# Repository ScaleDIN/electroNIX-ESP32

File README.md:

# electroNIX → ESP32 rewiring guide

**Use `BOARD_ELECTRONIX_4` for any 4-tube build and `BOARD_ELECTRONIX_4_6T`
for any 6-tube build.** These two board definitions cover every supported
TESTA-QUADRA PCB. The Nick2 IN-12 is a completely different design and is
documented separately below.

If you are retrofitting an older board that uses an **IRF840** boost MOSFET
(electroNIX 2 PCB, fourTINY) rather than the logic-level **IRLR3110Z** of the
electroNIX 4, you need a gate driver — see the *IRF840 boards* section under
electroNIX 4+S.

> ## ⚠️ 170 V is present on every board
> The boost output and all the driver stages carry ~170 VDC. The output
> capacitors hold charge after power-off. Unplug, wait, and verify with a
> meter before touching anything. Never rewire with power applied.

## Strategy: leave the ATmega in place, hold it in reset

You don't have to desolder the TQFP-44 on any of these boards. Grounding its
**RESET (pin 4)** puts every AVR pin into high-impedance, freeing all the
driver nets. One short wire from the RESET pad (or the ISP header JP1) to GND
and the chip is out of the picture.

Pick up the signals at the **resistors** they feed — larger pads, no
fine-pitch soldering. Every driver on every board is an active-high NPN base
behind a series resistor, so 3.3 V logic drives them directly with no level
shifters needed on any output.

---

# electroNIX 4 — recommended 4-tube target

`#define BOARD BOARD_ELECTRONIX_4`

Logic-level **IRLR3110Z** boost switch — drives directly from 3.3 V, no gate
driver needed.

## Signal map

| Net | Tap point | ESP32 GPIO | Notes |
|---|---|---|---|
| `C_0`…`C_9` cathodes | **R22–R31** (33 k) | 13, 14, 21, 22, 23, 25, 26, 27, 32, 33 | Designators are not in net order — see below. |
| `W_1`…`W_4` anodes | **R15, R14, R17, R16** (33 k) | 16, 17, 18, 19 | |
| `SEC_0`, `SEC_1` colons | **R18, R19** (430 k) | 4, 5 | See *Colon wiring* in the 4+S section. |
| `PWM` boost gate | **R59** (10 Ω at Q50) | 2 | IRLR3110Z, logic-level, drive directly. |
| `KOMP_170V` | **R60 / R61** junction | 35 (input) | |
| `JASNOSC` | **R63 / D1** junction | 34 (input) | R63 pulls up to **+5V_BUF** — lift its supply end and rewire to ESP32 **3V3** before connecting GPIO34. |
| `MEL` buzzer | **R62** (2 k) | **0** | GPIO0 is a strapping pin. Fit ≥10 kΩ pull-up to 3V3. `cfg.buzzerEn` defaults false. GPIO12 is free. |
| IR receiver (IR1) | IR1 pad | 39 (input, reserved) | Power IR1 from 3V3, not +5V_BUF. Not decoded yet. |
| DS3231 SDA (optional) | I2C bus | 1 | 4.7 kΩ pull-up to 3V3. |
| DS3231 SCL (optional) | I2C bus | 3 | 4.7 kΩ pull-up to 3V3. |
| Buttons S1–S3 | switch leg | 36 (optional) | External 10 k to 3V3 required — GPIO36 has no internal pull-up. |

GPIO1, GPIO3, and GPIO12 are all free when no DS3231 is fitted.

## Cathode designators are not in net order

This trips people up on every TESTA board: resistor numbers do not run in the
same order as `C_0`…`C_9`. Wire them in any convenient order, then fix any
scrambling in software using **Pin check** — you never have to resolder.

**Maintenance → Pin check → digits**: hold `0`, note what digit the tubes
actually show, repeat for `1`–`9`. Type the ten observations into the *Digits
shown for 0–9* field and save. The display is then correct. Re-open the page
and the field reads `0,1,2,…,9` — that's the confirmation.

**Tube positions** work the same way via *Pin check → tubes*: click each
position button, note which tube lights, record the physical order in *Tube
positions*. Digits and tube positions can be fixed independently and in either
order.

---

# electroNIX 4+S — recommended 6-tube target

`#define BOARD BOARD_ELECTRONIX_4_6T`

The electroNIX 4 expanded to six tubes with a seconds pair. Every cathode,
both colon outputs, the HV PWM pin, and all sensors stay on exactly the same
GPIOs as the 4-tube board. This definition also covers **fresh ESP32 retrofits
of the electroNIX 2 PCB** — use it in place of the obsolete
`BOARD_ELECTRONIX_2`.

## GPIO changes from the electroNIX 4

The electroNIX 4 uses all comfortable output GPIOs. The two extra anode
outputs and the optional LED backlight come from reassigning the buzzer and
reclaiming the two strapping pins:

| GPIO | Role on electroNIX 4 | Role on electroNIX 4+S |
|---|---|---|
| **0** | Unused | `MEL` buzzer (strapping pin — 10 kΩ pull-up to 3V3 required) |
| **12** | `MEL` buzzer | `W_5` anode — seconds tens tube (no pull-up needed) |
| **15** | Unused | `W_6` anode *or* LED backlight — see below (strapping pin — 10 kΩ pull-up to 3V3 required) |
| **1** | Free | DS3231 SDA — *or* `W_6` anode when LED backlight fitted |
| **3** | Free | DS3231 SCL |

## Pull-ups on GPIO0 and GPIO15

Both are strapping pins. GPIO0 drives the buzzer (normally LOW); GPIO15 drives
the W_6 anode or LED backlight BJT base through a 33 kΩ series resistor. Both
conditions pull those pins below the 2.31 V HIGH threshold at reset, which can
cause spurious download-mode entry.

**Fit 10 kΩ from GPIO0 to 3V3 and 10 kΩ from GPIO15 to 3V3.** GPIO12 (W_5)
is not a strapping pin and needs no pull-up.

## Colon wiring — SEC_0 and SEC_1

`SEC_0` (GPIO4) and `SEC_1` (GPIO5) are two independent drive outputs. The
firmware controls them with whatever colon mode is configured (STEADY, BLINK,
BREATHE, ALTERNATE, etc.) — what you connect to them is entirely up to you.
Common arrangements:

- **Single neon per colon position**: wire one neon to `SEC_0`, leave `SEC_1`
  unconnected. Set `BOARD_DUAL_NEON 0` in `board.h`.
- **Top and bottom dots, both positions**: wire all top neons in parallel to
  `SEC_0` and all bottom neons in parallel to `SEC_1`. ALTERNATE then steps
  top on → bottom on across all positions simultaneously.
- **Independent per-position control**: wire all HH:MM neons to `SEC_0` and
  all MM:SS neons to `SEC_1`.

Any arrangement works — the firmware fires GPIO4 and GPIO5 on every tick
regardless of what's physically connected. Set `BOARD_DUAL_NEON 1` whenever
two outputs are wired; set `BOARD_DUP_COLON 1` only if the web UI preview
should mirror the HH:MM colon state onto MM:SS (no firmware effect otherwise).

## Optional LED backlight (electroNIX 2 PCB only)

The electroNIX 2 PCB has an under-tube LED backlight chain (R17 → Q3). To
enable it:

1. **Wire R17 to GPIO15.** GPIO15 becomes `PIN_LEDBL`, PWM'd at 1 kHz. The
   10 kΩ pull-up already fitted on GPIO15 is sufficient.
2. **Wire W_6 (R42) to GPIO1.** GPIO1 was the original LED drive pin before
   the DS3231 retrofit; it reverts to active use here. The bootloader drives
   it briefly at reset — through a 33 kΩ base resistor with no HV on the
   rail, the tube cannot strike.
3. **Set `BOARD_HAS_LED_BL 1`** in the profile in `board.h`. The firmware
   remaps `ANODE_PINS[5]` to GPIO1 and sets `PIN_LEDBL = 15` automatically.
4. **Leave `BOARD_HAS_RTC 0`.** GPIO1 cannot be both W_6 and DS3231 SDA. The
   firmware issues a compile-time error if both flags are set.

## Signal map

| Net | Tap point | ESP32 GPIO | Notes |
|---|---|---|---|
| `C_0`…`C_9` cathodes | **R22–R31** (33 k) | 13, 14, 21, 22, 23, 25, 26, 27, 32, 33 | **Identical to the electroNIX 4.** |
| `W_1`…`W_4` anodes | **R15, R14, R17, R16** (33 k) | 16, 17, 18, 19 | **Identical.** |
| `W_5` anode (seconds tens) | 33 k base resistor | **12** | GPIO12, former buzzer. No pull-up needed. |
| `W_6` anode (seconds units) | 33 k base resistor | **15** *(no LED)* or **1** *(LED)* | See LED backlight section above. |
| `LED` backlight | **R17** (33 k, base of Q3) — electroNIX 2 PCB only | **15** *(when fitted)* | Mutually exclusive with DS3231 RTC. |
| `SEC_0`, `SEC_1` colons | 430 k base resistors | 4, 5 | **Identical to the electroNIX 4.** See *Colon wiring* above. |
| `PWM` boost gate | **R59** (10 Ω at Q50) | 2 | IRLR3110Z, logic-level. Identical. |
| `KOMP_170V` | **R60 / R61** junction | 35 (input) | Identical. |
| `JASNOSC` | **R63 / D1** junction | 34 (input) | Lift R63's +5V_BUF end to 3V3. Identical. |
| `MEL` buzzer | **R62** (2 k) | **0** | Strapping pin. 10 kΩ pull-up to 3V3. `cfg.buzzerEn` defaults false. |
| DS3231 SDA (optional) | I2C bus | **1** *(no LED)* | Unavailable when LED backlight fitted. 4.7 kΩ pull-up to 3V3. |
| DS3231 SCL (optional) | I2C bus | 3 | 4.7 kΩ pull-up to 3V3. |
| Buttons S1–S3 | switch leg | 36 (optional) | External 10 k to 3V3. |

## Matching the seconds tubes

Seconds tubes often sit behind different emitter resistors and look dimmer at
equal duty. Use the **per-tube trim** row in the web UI — six percentages — to
even them out without touching the hardware.

## IRF840 boards — gate driver required

The electroNIX 2 PCB and fourTINY use an **IRF840** boost MOSFET. This is a
standard-level part specified at Vgs = 10 V; at 3.3 V it will either not turn
on at all or turn on partially and overheat. **Fit a gate driver before
connecting the PWM wire.** Options:

1. **Gate driver (recommended):** TC4420, MCP1407, or UCC27517 from the
   board's +12 V rail. ESP32 GPIO2 → driver input, driver output → gate
   resistor → Q5 gate. Non-inverting — leave `HV_PWM_INVERT 0`.
2. **Discrete level shifter:** a 2N7002 with a pull-up to +12 V. This
   **inverts** — set `HV_PWM_INVERT 1`. Check Q5 doesn't run hot; the 2N7002
   is slower than a real driver.
3. **Swap the FET:** replace with a logic-level 500 V part. Uncommon;
   options 1 and 2 are usually easier.

The sketch refuses to build for an IRF840 board until `HV_GATE_FITTED 1` is
set in `board.h` — this is deliberate.

Also check the gate resistor on the fourTINY: **R50** is shown as 10 k on
that schematic, which may be a pull-down rather than a series resistor — 10 k
in series with the gate at 32 kHz is far too slow. Confirm with a meter before
powering up.

---

# Nick2 IN-12 — different architecture

`#define BOARD BOARD_NICK2`

The Nick2 is not a TESTA-QUADRA board. Where TESTA drives cathodes directly
from individual GPIOs, Nick2 uses a **74141 BCD decoder** — four GPIO bits
select which of the ten cathodes conducts, so a single chip replaces ten
transistors. The colon is a column of **five WS2812B addressable LEDs** rather
than neon lamps.

## Signal map (schematic rev 2.0, 2021-03-09)

| Net | ESP32 GPIO | Notes |
|---|---|---|
| 74141 input A (LSB) | 4 | BCD digit select — shared across all tubes. |
| 74141 input B | 17 | |
| 74141 input C | 5 | |
| 74141 input D (MSB) | 16 | |
| Anode 1 | 32 | One GPIO per tube — multiplexed by the ISR. |
| Anode 2 | 33 | |
| Anode 3 | 25 | |
| Anode 4 | 26 | |
| WS2812B chain | 3 (UART RX) | 5 LEDs per column: 1 decorative top, 2 colon dots, 1 colon dot, 1 decorative / warning bottom. |
| `JASNOSC` (optional) | 34 (input) | If a light sensor is fitted. |
| DS3231 SDA (optional) | 21 | Standard ESP32 I2C pins — no strapping-pin concerns. |
| DS3231 SCL (optional) | 22 | |

If your board revision uses different GPIOs, the runtime endpoint
`POST /api/action?do=setpin&kind=an&idx=0&gpio=32` writes to NVS and
reboots. `kind=an` for anode 0–3, `kind=bcd` for 74141 inputs A–D (0–3).
Alternatively define `PIN_BCD_A` etc. in `board.h` before including it.

## Colon LEDs

The five WS2812B LEDs are addressed 0–4 top to bottom. LEDs 1 and 3 (the two
colon dots) are driven by the colon mode; LEDs 0, 2, and 4 are decorative and
configurable separately. LED 4 (bottom) doubles as the *time not trusted*
warning — it blinks regardless of colon mode until a trusted time source
(NTP, RTC, or browser sync) is established.

If your column is physically upside-down, tick **colonReversed** in the web
UI to flip the mapping without rewiring.

---

# Deprecated board targets

The following board definitions remain in the firmware but are no longer
the recommended retrofit target. Use `BOARD_ELECTRONIX_4` or
`BOARD_ELECTRONIX_4_6T` for new builds.

## electroNIX 3 (`BOARD_ELECTRONIX_3`)

4-tube, logic-level IRLR3110ZPBF boost switch, **USB power only** (no 12 V
rail — a boost + diode-capacitor multiplier ladder runs directly from 5 V).
The GPIO map is identical to the electroNIX 4 except the light sensor pull-up
resistor is 1 M (R44) to +5V rather than +5V_BUF — lift it to 3V3 the same
way.

Only one colon neon is fitted from the factory (`SEC_0` only); a second can
be added as a bodge to the ATmega's PB1 pad and wired to GPIO5. Tick **Second
colon neon fitted** in the web UI once done.

Power: feed the ESP32's **5V/VIN** from `+5V_BUF` (D19 + bulk caps). Do not
feed a GPIO from the USB rail. The boost duty ceiling (`HV_DUTY_MAX` in
`display_testa.cpp`) may need raising on this board — watch `duty` and `hv`
in the status bar on first power-up.

## electroNIX 2 (`BOARD_ELECTRONIX_2` — obsolete)

PCB-030/031, 6-tube, **IRF840** boost switch. Use `BOARD_ELECTRONIX_4_6T`
for fresh retrofits of this PCB. A gate driver is required — see the *IRF840
boards* section above. Set `BOARD_HAS_LED_BL 1` if the under-tube LED
backlight chain (R17/Q3) is fitted. The cathode resistors are numbered R56–R65
in a scrambled order; use **Pin check** to sort them out in software rather
than reordering the wires.

## fourTINY (`BOARD_FOURTINY`)

4-tube (LC-516), **IRF840** boost switch — gate driver required. GPIO map is
identical to the electroNIX 4; use `BOARD_ELECTRONIX_4` for new builds unless
you have a specific reason to keep `BOARD_FOURTINY`. Confirm R50 is a
pull-down (not a series gate resistor) before powering up.

---

# Shared notes

## Power

**Do not power the ESP32 from the 78M05.** WiFi current peaks (300–500 mA)
dissipate ~3 W in a linear regulator fed from 12 V. Either:

1. Replace U1 with a pin-compatible switcher (OKI-78SR-5/1.5-W36-C, Traco
   TSR 1-2450) and feed the ESP32's **5V/VIN** from the board's 5 V rail, or
2. Add a small buck module (MP1584 / "mini-360" set to 5 V) from the 12 V
   input directly to the ESP32's **5V/VIN**, leaving the 78M05 to serve the
   original 5 V loads.

Never feed `+5V_BUF` into an ESP32 GPIO. The 3V3 pin powers only the
`JASNOSC` pull-up and any button pull-ups.

## Drive strength

At 3.3 V through 33 k base resistors the MPSA42 switches get ~80 µA of base
drive — enough for typical cathode current, but with less margin than at 5 V.
If a digit looks dim or ghosting appears, parallel the relevant 33 k with
another 33 k (or drop to 10 k). Most builds don't need this.

## Bring-up procedure

1. Set `BOARD` in the sketch. Wire everything **except** the `PWM` line.
   Ground the ATmega's RESET.
2. Power up. The ESP32 starts an access point **ElectroNIX-Setup** (password
   `nixie1234`). Connect, open `http://192.168.4.1`, enter WiFi and timezone,
   save — it reboots and joins your network as `http://electronix.local`.
3. Check the status bar: **HV** should read ≈0 V and duty should climb, then
   report *FAULT* after about a second — that's the sense-fault protection
   confirming the feedback wire on GPIO35 is being read. Power-cycle to clear.
4. Power off, discharge, connect the `PWM` wire (through the gate driver on
   IRF840 boards). Power on: HV should ramp to 170 V within a second and the
   tubes light. Measure the real voltage and set *HV sense trim* so the
   reported value matches.
5. Fix any digit or tube-order scrambling with **Pin check** as described in
   the electroNIX 4 section above.

## Settings and firmware updates

From **2.13.0** settings survive firmware updates — each setting lives under
its own NVS key, so a new version that adds a setting finds that key missing
and uses its default; everything else is read back untouched.

Use **Back up settings** and **Restore** before flashing anything
experimental or when setting up a second clock. The wiring order and per-tube
trims come along with it; the WiFi password is deliberately excluded.

## Running without NTP

Three fallbacks in order of accuracy:

1. **NTP** — shown as `time  NTP · 3m ago` in the status bar. Default poll
   interval 60 minutes, adjustable from 5 minutes to a day; *correct smoothly*
   slews rather than steps, so corrections never make seconds tubes skip.
2. **Browser sync** — opening the web page silently takes the time from your
   device if no network time is available. Works over the clock's own AP with
   no internet at all.
3. **Restored estimate** — written to flash hourly, shown as *estimated* in
   amber until a real sync arrives.

For a permanently offline clock, add a DS3231 — see below.

## Cleaning cycles

Nixie cathodes that rarely light can develop a haze; running them clears it.
Under *Maintenance*, set **Cleaning cycle** (how often, in minutes; 0 to
disable), **Cycle length** (1–60 seconds), and **Cycle style**:

- *Slot machine* — all tubes spin, then settle one at a time from the left.
- *Every digit in turn* — steps through 0–9 in equal slices, offset per tube.
  This one actually does the job: every cathode gets exactly the same
  conduction time.

## If the display flickers

**Check the status bar first.** The second line shows **core 0 / core 1**
load, **mux** (multiplex interrupt rate as a percentage of expected 40 kHz),
and **hv cuts**.

- **mux dips below 100%** — an interrupt stalled. From 2.15.0 the time
  snapshot is written to RTC memory (free, survives resets) and flash only
  every six hours, and that write waits for tubes-dark moments. If mux still
  dips, check that *Core Debug Level* is set to **None** in the IDE.
- **hv cuts climbing** — the boost regulator backed off on a noisy ADC sample.
  Check the HV sense trim calibration and the smoothing capacitors at the boost
  output (C2–C5 on the v4 schematic).

OTA updates deliberately blank the display for the transfer duration and then
reboot — a clean blank rather than a flicker is intentional.

**Arduino IDE settings that matter:**
- CPU Frequency: **240 MHz**
- Core Debug Level: **None**
- Erase All Flash Before Sketch Upload: **Disabled** (unless you want to lose settings)

## If the light sensor isn't doing anything

The status bar shows the sensor live as `light  1840 mV · 42%`. Watch it
while you cover the phototransistor.

1. **Reading says "railed" and never moves** — the 5 V pull-up mod hasn't
   been done. Lift the supply end of R63 (v4) / R11 (v2) / R57 (fourTINY) /
   R44 (v3) and rewire to ESP32 **3V3**.
2. **Reading moves but the tubes don't** — auto brightness must be ticked on.
   Also check that *min* and *max* aren't set to the same value.
3. **Moves over a narrow band** — calibrate using *use current as dark* and
   *as bright* in the web UI. A wider calibration span reduces the effect of
   ADC noise.
4. **Noisy reading** — add **100 nF ceramic** from GPIO34 to GND. This alone
   usually fixes it; the high-impedance pull-up can't recharge the ADC's
   sampling capacitor fast enough without it. Also consider lowering the
   pull-up from 1 M to 100 k, keeping the sensor wire short, and routing it
   away from the boost inductor.

---

# DS3231 real-time clock (optional, all boards)

A battery-backed DS3231 module lets the clock wake at the correct time
immediately after a mains outage without waiting for NTP. The status panel
shows **RTC** in green rather than *estimated* in amber.

## Enable in firmware

In `board.h`, above the `#define BOARD` line:

```c
#define BOARD_HAS_RTC 1
```

To override the default SDA/SCL pins:

```c
#define BOARD_RTC_SDA  0
#define BOARD_RTC_SCL 15
#define BOARD_HAS_RTC  1
```

## Default I2C pins

| Board family | SDA | SCL |
|---|---|---|
| All TESTA boards (4, 4+S, 3) | GPIO1 | GPIO3 |
| Nick2 IN-12 | GPIO21 | GPIO22 |

**4.7 kΩ pull-ups** from SDA to 3V3 and SCL to 3V3 are required. Most DS3231
breakout modules include them — check for R2/R3 on the silkscreen.

The DS3231 I2C pins are not strapping pins on any board. The 10 kΩ pull-up
requirements in the 4+S section above are for GPIO0 (buzzer) and GPIO15
(anode / LED backlight) — not for the I2C lines.

## Fit the CR2032 before powering up

Without it the DS3231 loses its time the moment the clock is unplugged. The
cell lasts several years in standby. When exhausted the DS3231 resets to
2000-01-01; the firmware detects this (year < 2020) and falls back to the NVS
epoch rather than displaying the year 2000.

## How it integrates with NTP

- **At boot**: the DS3231 is read before WiFi starts — the correct time
  appears within milliseconds, and `timeTrusted` is set immediately.
- **At NTP sync**: the DS3231 is updated to the NTP-corrected time.
- **Browser sync**: the posted epoch is written to the DS3231 and persists
  across power cuts — useful when NTP is blocked on your network.
- **No WiFi**: the DS3231 keeps time at ±2 ppm (≈ ±0.2 s/day) on the
  backup cell.

---

## Firmware safety features

- Boost gate is off during boot and flashing (GPIO2 boot pull-down).
- Software regulation: absolute duty clamp (~41 %), soft-start ramp, hard
  over-voltage cut at target + 12 V, shutdown if the feedback divider reads
  open — the converter will not run open-loop.
- HV shuts down whenever the tubes are off (night mode at 0 %, web toggle).
- 25 µs inter-digit blanking prevents ghosting between tubes.

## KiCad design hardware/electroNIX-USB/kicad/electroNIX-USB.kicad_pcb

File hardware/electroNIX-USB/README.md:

# electroNIX-USB — USB-C powered ESP32 nixie clock (4 or 6 × Z573M)

A new KiCad design: an ESP32 version of the TESTA-QUADRA **electroNIXclock 3**
(PCB-036, 2013). That was the micro-USB powered board; its schematic is filed as
`original electronix clock/z573m/schema_204xZ573M.pdf`. The tube is the RFT Z573M.
A Z566M variant comes later.

**Status (work in progress):** schematics are done for 4 and 6 tubes. The
4-tube PCB (`kicad/electroNIX-USB.kicad_pcb`, 102 × 66 mm, the original
kit's size) and the 6-tube PCB (`kicad-6tube/`, 150 × 66 mm) are **placed
but not routed**. Route them in KiCad (Freerouting plugin, fanout off),
then add the GND pours on both layers.

| Path | Contents |
|---|---|
| `kicad/` | **4-tube** KiCad project (HH:MM): root sheet plus 4 sub-sheets, project symbol library (`electronix.kicad_sym`: Z573M, `+170V`) and footprint library (`electronix.pretty`: `Nixie_RFT_Z573M`) |
| `kicad-6tube/` | **6-tube** KiCad project (HH:MM:SS), same layout of sheets |
| `electroNIX-USB-{4,6}tube-schematic.pdf` | Plots of all 5 sheets |
| `electroNIX-USB-{4,6}tube-bom.csv` | BOMs grouped by value and footprint |
| `source/gen.py` | Generator: `python3 source/gen.py kicad` or `python3 source/gen.py kicad-6tube --tubes 6` |
| `source/pcb.py` | Board builder: places parts from the netlist, autoroutes with Freerouting, pours GND, runs DRC (`--place-only` stops after placement) |
| `source/fab.sh` | Gerbers, drill files and pick-and-place zip for a board |
| `source/footprint.py` | Writes the Z573M footprint: `python3 source/footprint.py kicad/electronix.pretty` |

The files are in KiCad 7 format, so KiCad 7, 8 and 9 all open them (8 and 9
upgrade on save). Once you start editing in KiCad, the KiCad files are the
source and the generator is only a record of the first pass. Don't re-run it
over hand edits.

## Sheets

1. **Power & USB:** USB-C receptacle wired as a 5 V sink (5k1 on CC1/CC2),
   polyfuse, SMBJ5.0CA TVS, 22 µF/35 V tantalum bulk, USBLC6-2SC6 on D+/D−, AMS1117-3.3, and CH340C
   for programming and serial log.
2. **ESP32:** ESP32-WROOM-32E, two-transistor DTR/RTS auto-reset, and the
   light sensor. **No switches:** the firmware is set up from its web UI
   and reads no button. The CH340C resets the chip and puts it into
   download mode, and unplugging USB is the reset. If auto-reset ever
   fails, short the IO0 pull-up to GND while plugging in. No buzzer and
   no RTC: time
   comes from NTP.
3. **HV supply:** the PCB-036 converter. IO2 drives an IRLR3110Z into a
   33 µH WE 7447715330 (22 µH on the 6-tube build). The switch node feeds a
   7-diode / 7-capacitor Cockcroft-Walton ladder (10MQ100N, 2.2 µF/100 V)
   that makes 170 V. Feedback is 430k/6k2, the same ratio as
   `HV_DIV_RATIO`.
4. **Display:** 4 or 6 × Z573M. Anodes are switched high-side (MMBTA42
   level shift into MMBTA92, 5k6 or 3k9 anode resistor). 10 shared MMBTA42
   cathode switches. The 1N4148 off-cathode clamp to a ~32 V bias is kept
   from PCB-036. Colon neons.

## Z573M (RFT data book p.101/103)

Source: [frank.pocnet.net/sheets/084/z/Z573M.pdf](https://frank.pocnet.net/sheets/084/z/Z573M.pdf).
Z5730M is the same tube without the contrast-filter coating.

- **Tube:** side-view, 13 mm digits, decimal point on the right. Bulb is
  Ø19 × 47.6 mm with 38 mm flying leads.
- **Pinout:** 1–3 = k1–k3, 4 = ic (internal, leave open), 5–9 = k4–k8,
  10 = dp, 11 = k9, 12 = k0, 13 = anode. This matches the symbol.
- **Lead layout:** 13 leads on a **Ø9.53 mm** circle in 14 equal
  positions (25.7°), with the gap opposite **wire 7, which faces the
  front**.
- **Electrical:** V_ign 150 V, V_maint 140 V, V_ext 120 V, minimum supply
  170 V. **Cathode current 1.5–2.5 mA continuous, 12 mA pulse maximum.**

### Footprint `electronix:Nixie_RFT_Z573M`

- **Geometry:** a top view with wire 7 toward +Y, so the board's front
  edge goes toward +Y. The data book draws the leads from below,
  numbered clockwise; on the footprint they run counter-clockwise. Pad 1
  is square.
- **Pads:** 0.8 mm drill, 1.35 mm pad, 2.12 mm centre spacing.
- **Silkscreen:** references are 0.8 mm. Each sits right beside its own
  part (within ~1 mm, and closer to its own part than to any other) or,
  where there's no room, inside the part between its pads (the ladder
  caps). Labels never overlap other labels, part outlines, pads or the
  board edge.
- **KBIAS network** (430k, 100k, 4 × 470 nF series string) sits in the
  free space under the colon, between the tube 2 and tube 3 anode
  clusters.
- **ESP32 footprint:** the stock footprint's 48 mm-wide keep-out and
  matching courtyard are replaced by a body-sized courtyard plus a board
  keep-out under the antenna. The module sits 0.3 mm inside the back edge.
  Minimum drill is 0.2 mm for the module's exposed-pad vias.
- **Known DRC item:** the USB-C footprint's locating pegs are 0.19 mm from
  its own pads (stock GCT USB4105 footprint). Exclude it in DRC.
- **Net classes:** HV (0.4 mm clearance) for +170 V, anodes, the ladder
  and the neon nets; Power (0.5 mm track) for GND/+5V/+3V3/VBUS.

## Open points (check before or during layout)

- **Neon footprints** are still unassigned. Pick the lamp (NE-2 or INS-1)
  with the layout.
- **WE 7447715330:** the KiCad footprint is WE-PD "Typ LS" (12 × 12 mm),
  which is the same series as the 7447715906 in its datasheet link.
  Confirm 33 µH and the saturation current (≥ 2.5 A) when ordering. For
  the 6-tube build's 22 µH, `7447715220` is inferred from the same part
  numbering: check that it exists and that I_sat ≥ 3 A.
- **ERC:** the KiCad 7 command line here has no ERC, so I checked
  connectivity on the exported netlist instead. No single-pin nets, every
  driver chain was traced, and the multiplier matches PCB-036 diode for
  diode. Run *Inspect → ERC* once in KiCad. Expect a few "power input not
  driven" warnings that the PWR_FLAGs should already cover.

## Z566M and other tubes

Only sheet 5 changes: the tube symbol and footprint, and the anode
resistor. The tube count is already a generator option. The Z566M
(30 mm digits) still needs its data sheet for the pinout and lead layout.

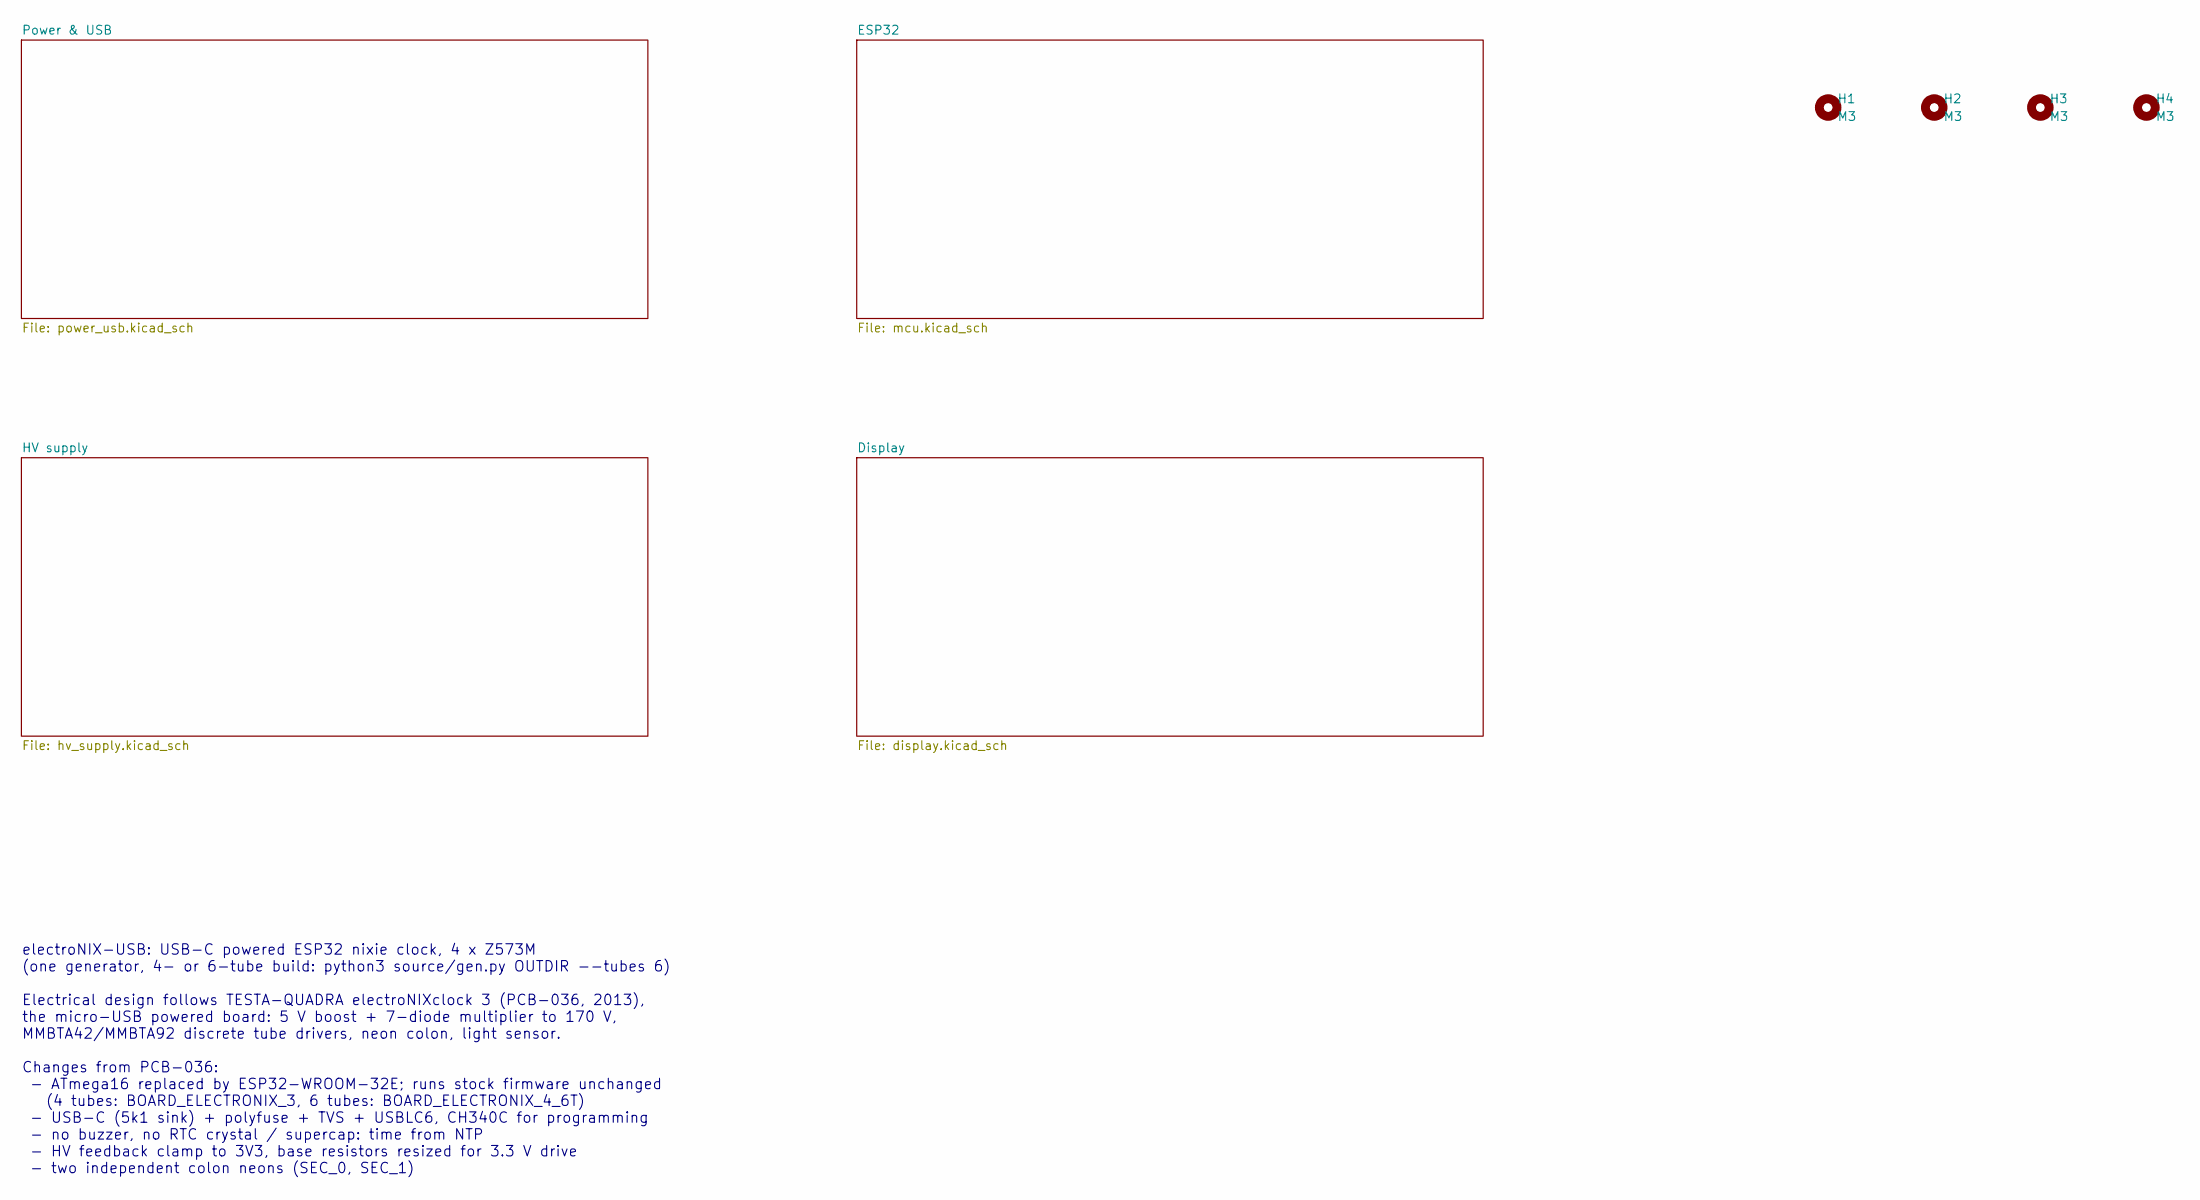
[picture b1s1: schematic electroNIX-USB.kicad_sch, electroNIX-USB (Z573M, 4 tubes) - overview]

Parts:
H1, H2, H3, H4: M3; MountingHole_3.2mm_M3

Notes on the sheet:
electroNIX-USB: USB-C powered ESP32 nixie clock, 4 x Z573M (one generator, 4- or 6-tube build: python3 source/gen.py OUTDIR --tubes 6) Electrical design follows TESTA-QUADRA electroNIXclock 3 (PCB-036, 2013), the micro-USB powered board: 5 V boost + 7-diode multiplier to 170 V, MMBTA42/MMBTA92 disc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

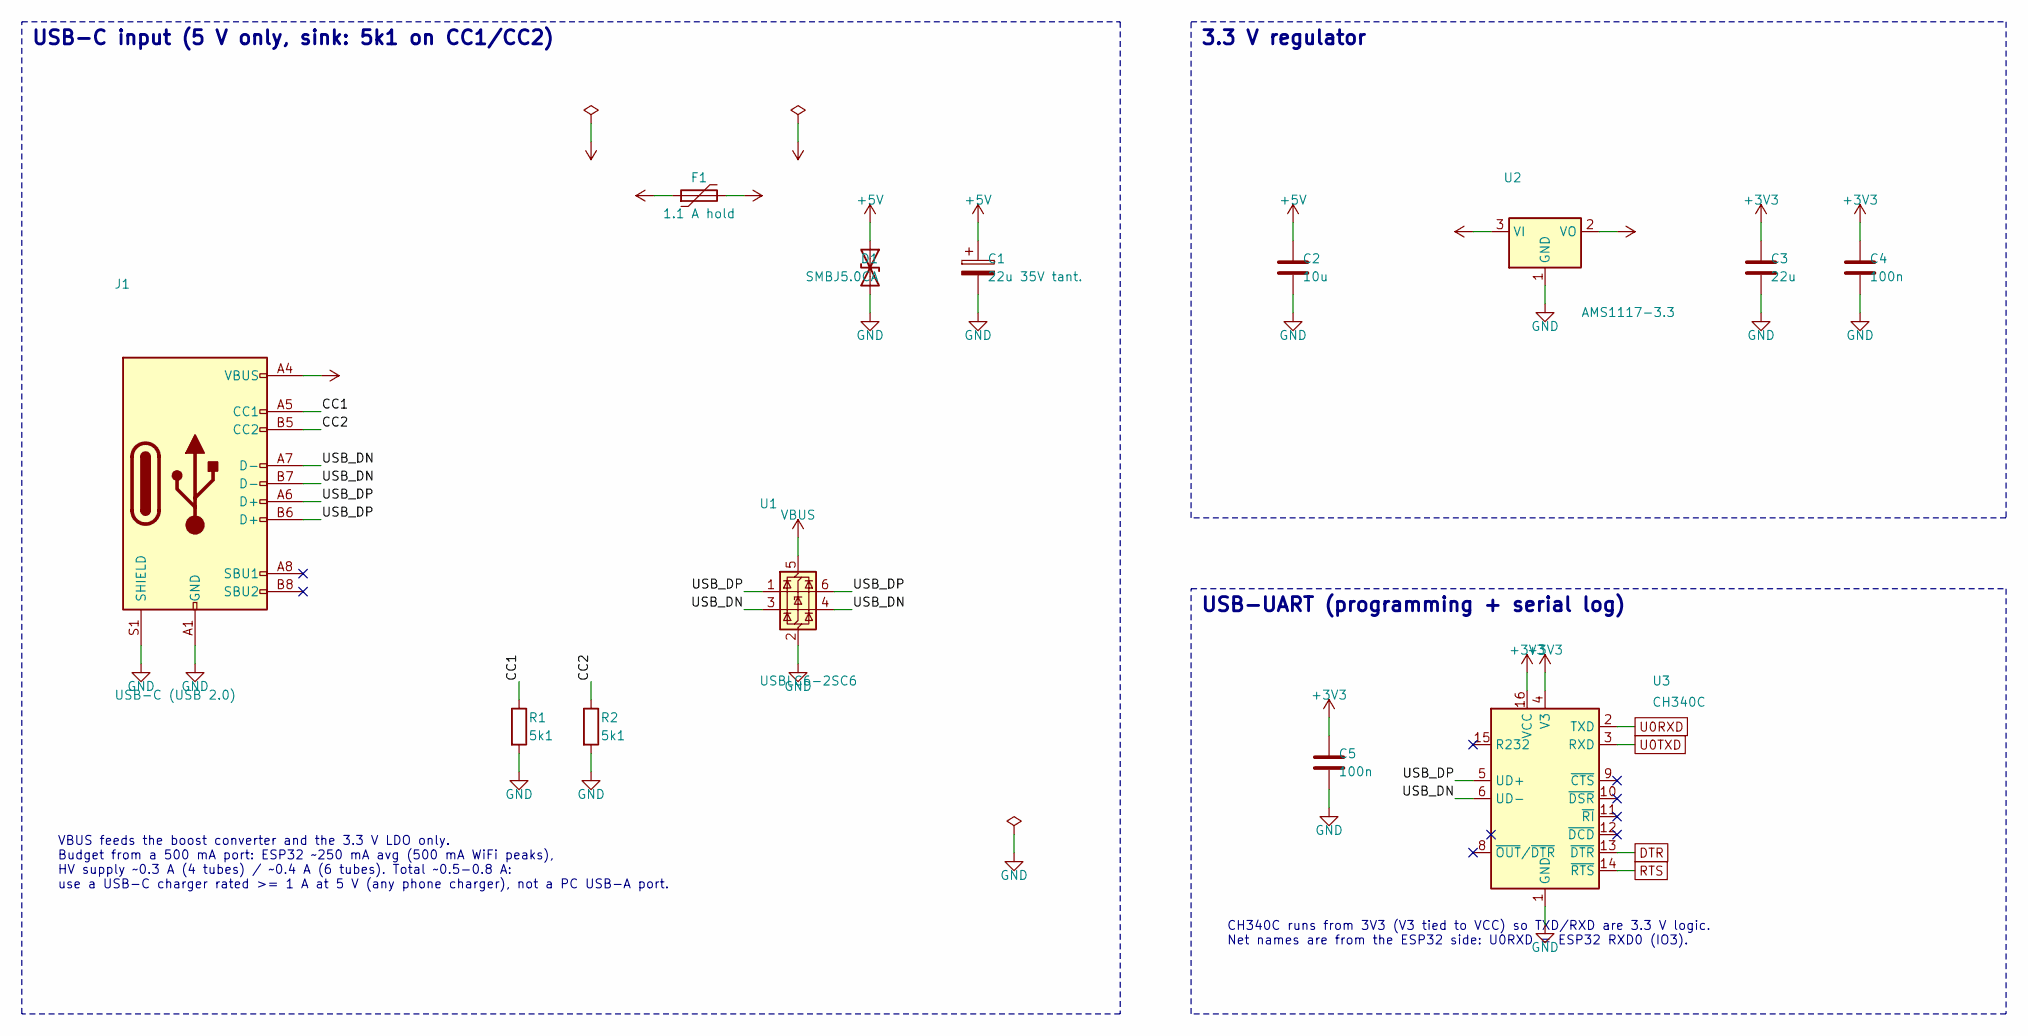
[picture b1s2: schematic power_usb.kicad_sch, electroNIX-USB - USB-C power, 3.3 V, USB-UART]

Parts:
C1: 22u 35V tant.; CP_EIA-7343-31_Kemet-D
C2: 10u; C_1206_3216Metric
C3: 22u; C_1206_3216Metric
C4, C5: 100n; C_0805_2012Metric
D1: SMBJ5.0CA; D_SMB
F1: 1.1 A hold; Fuse_1206_3216Metric
J1: USB-C (USB 2.0); USB_C_Receptacle_GCT_USB4105-xx-A_16P_TopMnt_Horizontal
R1, R2: 5k1; R_0805_2012Metric
U1: USBLC6-2SC6; SOT-23-6
U2: AMS1117-3.3; SOT-223-3_TabPin2
U3: CH340C; SOIC-16_3.9x9.9mm_P1.27mm

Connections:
+3V3: C3.1, C4.1, C5.1, U2.2 (VO), U3.4 (V3), U3.16 (VCC); also elsewhere on the board
+5V: C1.1, C2.1, D1.1 (A1), F1.2, U2.3 (VI); also elsewhere on the board
/Power & USB/CC1: J1.A5 (CC1), R1.1
/Power & USB/CC2: J1.B5 (CC2), R2.1
/Power & USB/USB_DN: J1.A7 (D-), J1.B7 (D-), U1.3 (I/O2), U1.4 (I/O2), U3.6 (UD-)
/Power & USB/USB_DP: J1.A6 (D+), J1.B6 (D+), U1.1 (I/O1), U1.6 (I/O1), U3.5 (UD+)
DTR: U3.13 (~DTR); also elsewhere on the board
GND: C1.2, C2.2, C3.2, C4.2, C5.2, D1.2 (A2), J1.A1 (GND), J1.A12 (GND), J1.B1 (GND), J1.B12 (GND), J1.S1 (SHIELD), R1.2, R2.2, U1.2 (GND), U2.1 (GND), U3.1 (GND); also elsewhere on the board
RTS: U3.14 (~RTS); also elsewhere on the board
U0RXD: U3.2 (TXD); also elsewhere on the board
U0TXD: U3.3 (RXD); also elsewhere on the board
VBUS: F1.1, J1.A4 (VBUS), J1.A9 (VBUS), J1.B4 (VBUS), J1.B9 (VBUS), U1.5 (VBUS)

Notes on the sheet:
USB-C input (5 V only, sink: 5k1 on CC1/CC2)
VBUS feeds the boost converter and the 3.3 V LDO only. Budget from a 500 mA port: ESP32 ~250 mA avg (500 mA WiFi peaks), HV supply ~0.3 A (4 tubes) / ~0.4 A (6 tubes). Total ~0.5-0.8 A: use a USB-C charger rated >= 1 A at 5 V (any phone charger), not a PC USB-A port.
3.3 V regulator
USB-UART (programming + serial log)
CH340C runs from 3V3 (V3 tied to VCC) so TXD/RXD are 3.3 V logic. Net names are from the ESP32 side: U0RXD = ESP32 RXD0 (IO3).

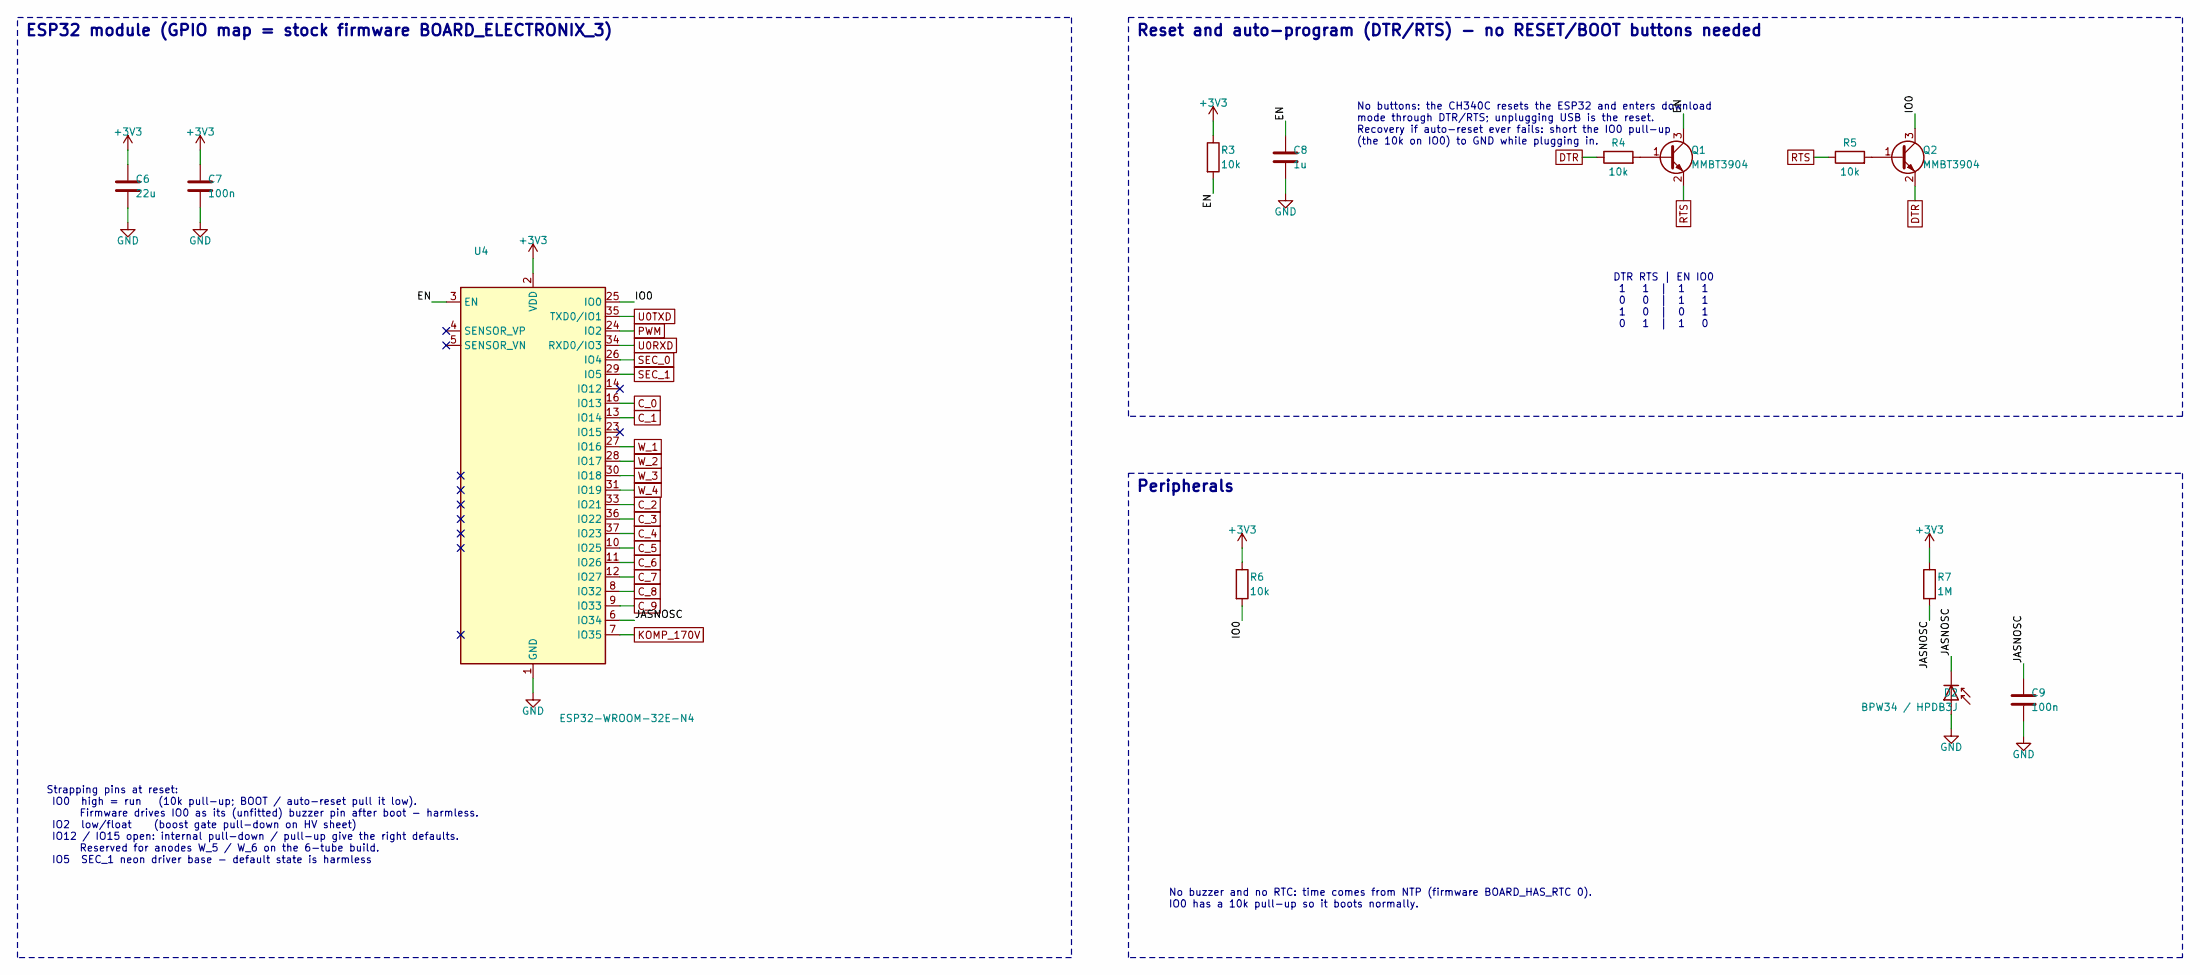
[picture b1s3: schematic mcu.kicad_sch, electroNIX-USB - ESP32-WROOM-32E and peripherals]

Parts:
C6: 22u; C_1206_3216Metric
C7, C9: 100n; C_0805_2012Metric
C8: 1u; C_0805_2012Metric
D2: BPW34 / HPDB3J; Osram_DIL2_4.3x4.65mm_P5.08mm
Q1, Q2: MMBT3904; SOT-23
R3, R4, R5, R6: 10k; R_0805_2012Metric
R7: 1M; R_0805_2012Metric
U4: ESP32-WROOM-32E-N4; ESP32-WROOM-32D

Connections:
+3V3: C6.1, C7.1, R3.1, R6.1, R7.1, U4.2 (VDD); also elsewhere on the board
/ESP32/EN: C8.1, Q1.3 (C), R3.2, U4.3 (EN)
/ESP32/IO0: Q2.3 (C), R6.2, U4.25 (IO0)
/ESP32/JASNOSC: C9.1, D2.1 (K), R7.2, U4.6 (IO34)
C_0: U4.16 (IO13); also elsewhere on the board
C_1: U4.13 (IO14); also elsewhere on the board
C_2: U4.33 (IO21); also elsewhere on the board
C_3: U4.36 (IO22); also elsewhere on the board
C_4: U4.37 (IO23); also elsewhere on the board
C_5: U4.10 (IO25); also elsewhere on the board
C_6: U4.11 (IO26); also elsewhere on the board
C_7: U4.12 (IO27); also elsewhere on the board
C_8: U4.8 (IO32); also elsewhere on the board
C_9: U4.9 (IO33); also elsewhere on the board
DTR: Q2.2 (E), R4.1; also elsewhere on the board
GND: C6.2, C7.2, C8.2, C9.2, D2.2 (A), U4.1 (GND), U4.15 (GND), U4.38 (GND), U4.39 (GND); also elsewhere on the board
KOMP_170V: U4.7 (IO35); also elsewhere on the board
unnamed: Q1.1 (B), R4.2
unnamed: Q2.1 (B), R5.2
PWM: U4.24 (IO2); also elsewhere on the board
RTS: Q1.2 (E), R5.1; also elsewhere on the board
SEC_0: U4.26 (IO4); also elsewhere on the board
SEC_1: U4.29 (IO5); also elsewhere on the board
U0RXD: U4.34 (RXD0/IO3); also elsewhere on the board
U0TXD: U4.35 (TXD0/IO1); also elsewhere on the board
W_1: U4.27 (IO16); also elsewhere on the board
W_2: U4.28 (IO17); also elsewhere on the board
W_3: U4.30 (IO18); also elsewhere on the board
W_4: U4.31 (IO19); also elsewhere on the board

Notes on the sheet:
ESP32 module (GPIO map = stock firmware BOARD_ELECTRONIX_3)
Strapping pins at reset: IO0 high = run (10k pull-up; BOOT / auto-reset pull it low). Firmware drives IO0 as its (unfitted) buzzer pin after boot - harmless. IO2 low/float (boost gate pull-down on HV sheet) IO12 / IO15 open: internal pull-down / pull-up give the right defaults. Reserved for anodes 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
Reset and auto-program (DTR/RTS) - no RESET/BOOT buttons needed
No buttons: the CH340C resets the ESP32 and enters download mode through DTR/RTS; unplugging USB is the reset. Recovery if auto-reset ever fails: short the IO0 pull-up (the 10k on IO0) to GND while plugging in.
DTR RTS | EN IO0 1 1 | 1 1 0 0 | 1 1 1 0 | 0 1 0 1 | 1 0
Peripherals
No buzzer and no RTC: time comes from NTP (firmware BOARD_HAS_RTC 0). IO0 has a 10k pull-up so it boots normally.

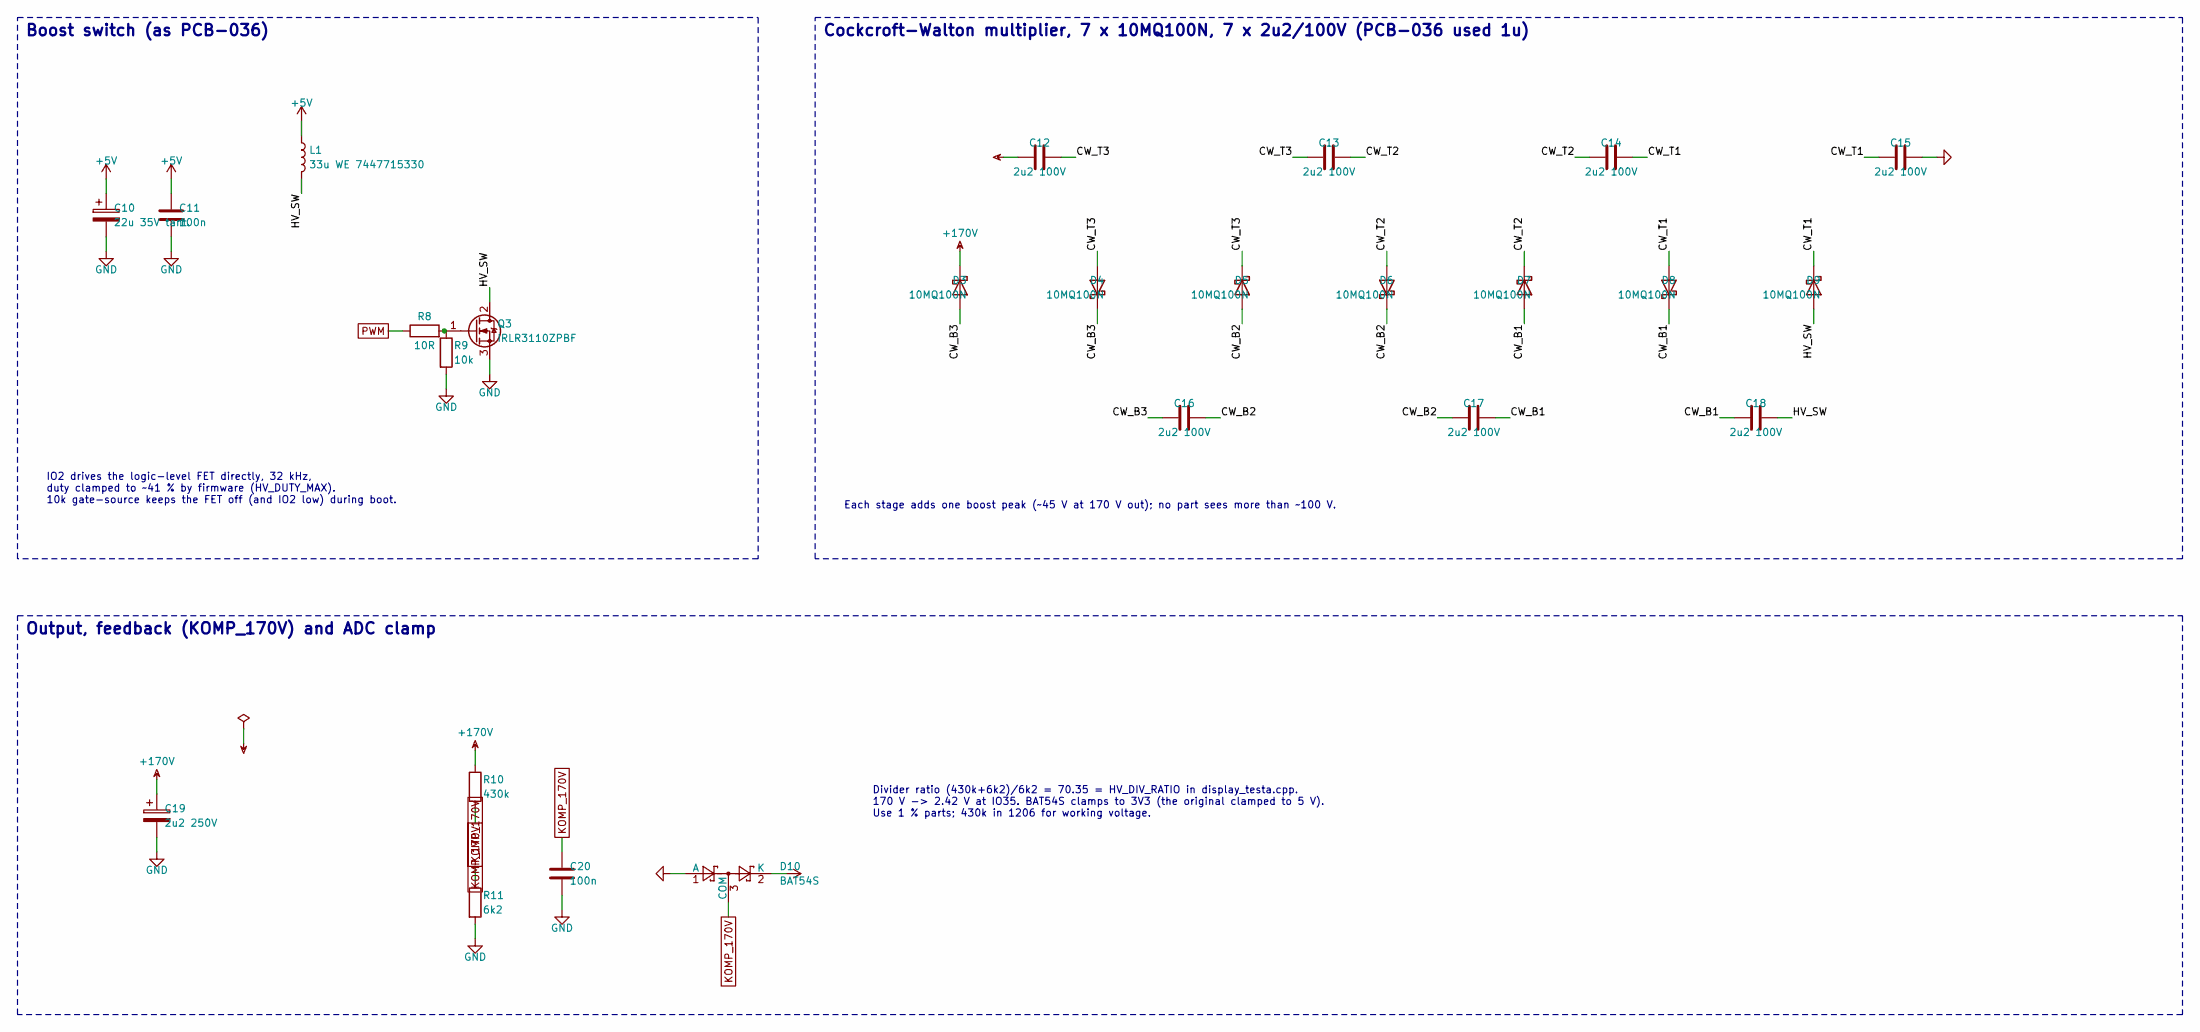
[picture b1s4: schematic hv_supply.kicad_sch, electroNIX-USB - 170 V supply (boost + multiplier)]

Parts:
C10: 22u 35V tant.; CP_EIA-7343-31_Kemet-D
C11, C20: 100n; C_0805_2012Metric
C12, C13, C14, C15, C16, C17, C18: 2u2 100V; C_1210_3225Metric
C19: 2u2 250V; CP_Radial_D8mm_P2.50mm_Lying
D3, D4, D5, D6, D7, D8, D9: 10MQ100N; D_SMA
D10: BAT54S; SOT-23
L1: 33u WE 7447715330; L_Wuerth_WE-PD-Typ-LS
Q3: IRLR3110ZPBF; TO-252-2
R8: 10R; R_0805_2012Metric
R9: 10k; R_0805_2012Metric
R10: 430k; R_1206_3216Metric
R11: 6k2; R_0805_2012Metric

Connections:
+3V3: D10.2 (K); also elsewhere on the board
+5V: C10.1, C11.1, L1.1; also elsewhere on the board
+170V: C12.1, C19.1, D3.1 (K), R10.1; also elsewhere on the board
/HV supply/CW_B1: C17.2, C18.1, D7.2 (A), D8.1 (K)
/HV supply/CW_B2: C16.2, C17.1, D5.2 (A), D6.1 (K)
/HV supply/CW_B3: C16.1, D3.2 (A), D4.1 (K)
/HV supply/CW_T1: C14.2, C15.1, D8.2 (A), D9.1 (K)
/HV supply/CW_T2: C13.2, C14.1, D6.2 (A), D7.1 (K)
/HV supply/CW_T3: C12.2, C13.1, D4.2 (A), D5.1 (K)
/HV supply/HV_SW: C18.2, D9.2 (A), L1.2, Q3.2 (D)
GND: C10.2, C11.2, C15.2, C19.2, C20.2, D10.1 (A), Q3.3 (S), R9.2, R11.2; also elsewhere on the board
KOMP_170V: C20.1, D10.3 (COM), R10.2, R11.1; also elsewhere on the board
unnamed: Q3.1 (G), R8.2, R9.1
PWM: R8.1; also elsewhere on the board

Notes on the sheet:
Boost switch (as PCB-036)
IO2 drives the logic-level FET directly, 32 kHz, duty clamped to ~41 % by firmware (HV_DUTY_MAX). 10k gate-source keeps the FET off (and IO2 low) during boot.
Cockcroft-Walton multiplier, 7 x 10MQ100N, 7 x 2u2/100V (PCB-036 used 1u)
Each stage adds one boost peak (~45 V at 170 V out); no part sees more than ~100 V.
Output, feedback (KOMP_170V) and ADC clamp
Divider ratio (430k+6k2)/6k2 = 70.35 = HV_DIV_RATIO in display_testa.cpp. 170 V -> 2.42 V at IO35. BAT54S clamps to 3V3 (the original clamped to 5 V). Use 1 % parts; 430k in 1206 for working voltage.

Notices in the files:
hardware/electroNIX-USB/kicad-6tube/display.kicad_sch:
Licensed with the repository; see LICENSE
